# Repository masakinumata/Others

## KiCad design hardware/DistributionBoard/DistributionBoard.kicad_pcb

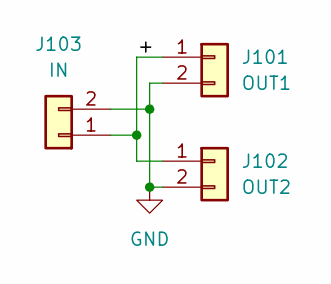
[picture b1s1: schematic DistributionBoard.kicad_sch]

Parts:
J101: OUT1; SolderWire-0.15sqmm_1x02_P4mm_D0.5mm_OD1.5mm
J102: OUT2; SolderWire-0.15sqmm_1x02_P4mm_D0.5mm_OD1.5mm
J103: IN; SolderWire-0.15sqmm_1x02_P4mm_D0.5mm_OD1.5mm

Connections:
/+: J101.1, J102.1, J103.1
GND: J101.2, J102.2, J103.2

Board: 2 copper layers, 3 parts (0 on the bottom side), 2 nets, no tracks yet.

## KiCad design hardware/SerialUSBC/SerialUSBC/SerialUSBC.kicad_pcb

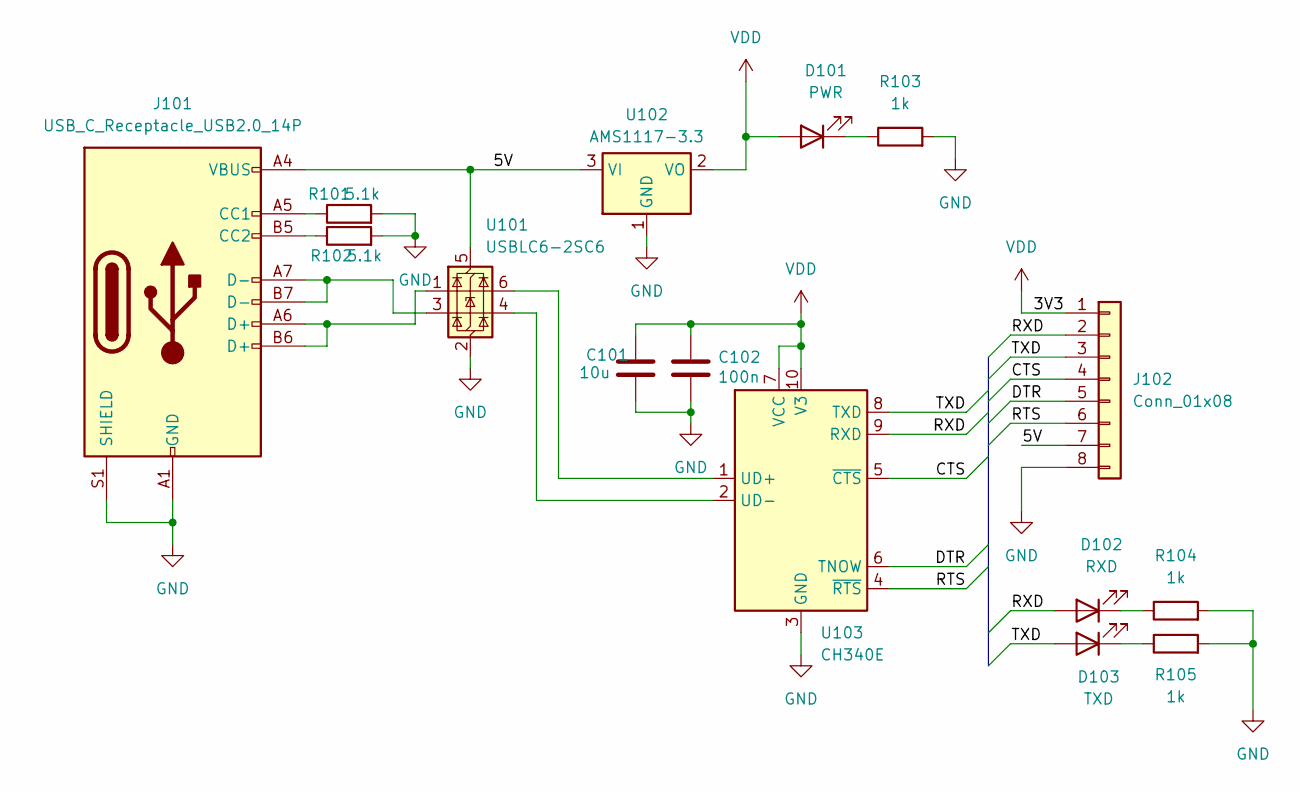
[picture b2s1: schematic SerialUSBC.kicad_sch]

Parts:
C101: 10u; C_0603_1608Metric; LCSC C96446
C102: 100n; C_0402_1005Metric; LCSC C1525
D101: PWR; LED_0805_2012Metric; LCSC C84256
D102: RXD; LED_0805_2012Metric; LCSC C2297
D103: TXD; LED_0805_2012Metric; LCSC C2297
J101: USB_C_Receptacle_USB2.0_14P; USB_C_Receptacle_G-Switch_GT-USB-7010ASV
J102: Conn_01x08; PinHeader_1x08_P2.54mm_Horizontal
R101, R102: 5.1k; R_0402_1005Metric; LCSC C25905
R103, R104, R105: 1k; R_0402_1005Metric; LCSC C11702
U101: USBLC6-2SC6; SOT-23-6
U102: AMS1117-3.3; SOT-223-3_TabPin2; LCSC C6186
U103: CH340E; MSOP-10_3x3mm_P0.5mm

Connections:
/5V: J101.A4 (VBUS), J101.A9 (VBUS), J101.B4 (VBUS), J101.B9 (VBUS), J102.7, U101.5 (VBUS), U102.3 (VI)
/CTS: J102.4, U103.5 (~CTS)
/DTR: J102.5, U103.6 (TNOW)
/RTS: J102.6, U103.4 (~RTS)
/RXD: D102.2 (A), J102.2, U103.9 (RXD)
/TXD: D103.2 (A), J102.3, U103.8 (TXD)
GND: C101.2, C102.2, J101.A1 (GND), J101.A12 (GND), J101.B1 (GND), J101.B12 (GND), J101.S1 (SHIELD), J102.8, R101.2, R102.2, R103.2, R104.2, R105.2, U101.2 (GND), U102.1 (GND), U103.3 (GND)
unnamed: D101.1 (K), R103.1
unnamed: D102.1 (K), R104.1
unnamed: D103.1 (K), R105.1
unnamed: J101.A5 (CC1), R101.1
unnamed: J101.B5 (CC2), R102.1
unnamed: J101.A6 (D+), J101.B6 (D+), U101.1 (I/O1)
unnamed: J101.A7 (D-), J101.B7 (D-), U101.3 (I/O2)
unnamed: U101.6 (I/O1), U103.1 (UD+)
unnamed: U101.4 (I/O2), U103.2 (UD-)
VDD: C101.1, C102.1, D101.2 (A), J102.1, U102.2 (VO), U103.7 (VCC), U103.10 (V3)

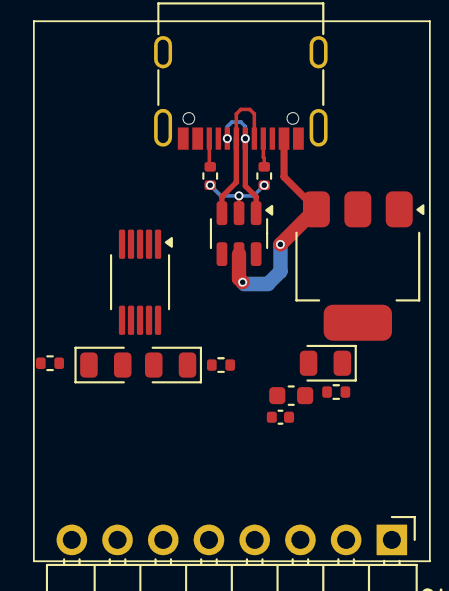
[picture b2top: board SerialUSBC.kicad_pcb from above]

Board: 2 copper layers, 15 parts (0 on the bottom side), 17 nets.

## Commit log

2026-02-07 Kicad
2026-02-08 発注できる
2026-02-09 4層にしてみた
2026-02-11 いろいろ
2026-02-12 一旦動くもの完成
2026-02-12 グラフ分け，通信ステータス
2026-02-15 キャリブレーション機能の追加
2026-02-15 UI上でのサーミスタの名前変更
2026-02-19 シリアル変換自作Project始動
2026-03-30 表面と裏面に分割
